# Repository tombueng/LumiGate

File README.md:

# LumiGate

**Art-Net / sACN (E1.31) → DMX512 Gateway** based on ESP32 / ESP32-S3 / WT32-ETH01 with a live web UI, WebSocket push, and manual DMX control via browser.

| Status page | Settings page |
|---|---|
|  |  |

### Web UI walkthrough

A guided tour of every control — manual channel control, labels, sparkline history, identify, blackout, and all settings:

▶ **[Watch the full walkthrough on YouTube](https://youtu.be/up8lIbRqosQ)** &nbsp;·&nbsp; regenerate with [`docs/screenshot.mjs`](docs/screenshot.mjs)

---

## Features

| Feature | Details |
|---|---|
| **Art-Net → DMX512** | Full 512-channel, unicast or broadcast, universe configurable (0–15) |
| **sACN / E1.31 → DMX512** | Multicast receive, universe configurable, runs alongside Art-Net |
| **Protocol selection** | Art-Net only / sACN only / Both — configurable in web UI |
| **Live Web UI** | Bootstrap 5 dark theme, WebSocket push (~10/s), all 512 channels visible |
| **Sender list** | Shows all active Art-Net / sACN senders with per-sender FPS |
| **Conflict detection** | Warning banner when multiple senders are active simultaneously |
| **Jitter stat** | Real-time inter-frame timing deviation (EMA) |
| **Change log** | Live log of DMX value changes with top-N changed channels per frame |
| **Sparkline** | Per-channel history sparkline in the channel detail modal |
| **Channel labels** | Name any channel (e.g. "Front Wash L") — shown in grid, modal, and change log |
| **Identify** | Flash a channel to full for ~1.5 s to physically locate the fixture |
| **Manual DMX control** | Click any channel in browser, set value via slider |
| **Blackout button** | Zero all channels instantly from browser |
| **Art-Net / Manual toggle** | Switch between protocol passthrough and manual override |
| **Failsafe output** | Continuous 40 Hz DMX refresh holds the last frame through brief input gaps |
| **Static IP or DHCP** | Configurable static IP/gateway/subnet/DNS, or automatic DHCP |
| **Mesh-aware WiFi** | Scans all channels and joins the **strongest** AP (multi-AP/mesh friendly) |
| **WiFi Config Portal** | First-boot AP + captive portal via WiFiManager |
| **Versioned OTA** | Pick & install any past release from a table, or auto-update to latest |
| **OTA Updates** | ArduinoOTA (IDE/CLI) + manual `.bin` upload + one-click GitHub update |
| **mDNS** | Reachable as `dmx-gateway.local` (hostname configurable) |
| **REST API** | `GET /dmx.json`, `/senders.json`, `/log.json`, `/version.json`, `/labels.json` |
| **Status LED** | Plain GPIO or WS2812 RGB NeoPixel — color codes WiFi/idle/DMX active state |
| **Up to 2 DMX outputs** | Two independent universes, each its own UART + RS485 transceiver (same universe on both = splitter) |
| **Status display** | Optional I²C OLED (SSD1306 / SH1106) or colour SPI OLED (SSD1351) — IP, universe, FPS, sources + auto-rotating conflict/identify/manual banners |
| **Configurable DMX pins** | Per output: universe, UART port, TX / RX / RTS GPIO — set at runtime via web UI, no recompile |
| **NVS persistence** | Universe, protocol, IP config, labels, hostname, OTA password, LED/DMX pin config survive reboots |
| **Config reset** | Hold BOOT button 3 s on startup, or via `/reset` page |
| **Ethernet support** | WT32-ETH01: wired LAN via LAN8720, no WiFi required, DHCP |
| **Dual/triple target** | Builds for ESP32 (WROOM-32), ESP32-S3 (DevKitC-1), WT32-ETH01 |

---

## Hardware

> ### 🛠 Custom PCB — LumiGate v3
>
> Want the real thing instead of breadboard + modules? There's a complete **open-source 4-layer PCB**:
> ESP32-S3 with **both WiFi and wired Ethernet** (W5500), **galvanically-isolated DMX** output,
> USB-C power + flashing, status LEDs, BOOT/RST buttons, and an optional OLED/TFT display header —
> all palm-sized and fabricable at JLCPCB for a few dollars.
>
> 
>
> **→ Full design, component rationale, BOM, gerbers & JLCPCB fab guide: [`hardware/`](hardware/README.md)**

The rest of this section covers the simpler **breadboard / module** build (an off-the-shelf ESP32 DevKit
+ an isolated RS485 module) — perfect for getting started without fabricating a board.

### Bill of Materials — WiFi build (ESP32 / ESP32-S3)

| # | Component | Description | Link |
|---|---|---|---|
| 1 | **ESP32 DevKit v1** | ESP32-WROOM-32, 30-pin, any CH340/CP2102 variant | [Amazon.de search](https://www.amazon.de/s?k=ESP32+DevKit+WROOM-32) |
| 2 | **Waveshare TTL to RS485 (C)** | Galvanically isolated RS485 transceiver, auto-direction | [Amazon.de – B0D4TZQYVG](https://www.amazon.de/dp/B0D4TZQYVG) |
| 3 | **XLR-5 female panel socket** | Standard DMX output connector (XLR-3 also works) | [Amazon.de search](https://www.amazon.de/s?k=XLR+5+Pin+Buchse+Panel) |
| 4 | **Jumper wires / dupont cables** | Male–male for breadboard, or direct solder | any |
| 5 | **USB-A to Micro-USB cable** | Power + serial flash | any |

### Bill of Materials — Ethernet build (WT32-ETH01)

| # | Component | Description | Link |
|---|---|---|---|
| 1 | **WT32-ETH01** | ESP32 + LAN8720 Ethernet PHY, built-in RJ45 | [Amazon.de search](https://www.amazon.de/s?k=WT32-ETH01) |
| 2 | **Waveshare TTL to RS485 (C)** | Same as WiFi build | [Amazon.de – B0D4TZQYVG](https://www.amazon.de/dp/B0D4TZQYVG) |
| 3 | **XLR-5 female panel socket** | Same as WiFi build | any |
| 4 | **Ethernet cable** | Cat5e or better | any |
| 5 | **5V power supply** (500 mA+) | WT32-ETH01 has no USB port — use a 5V supply on the VIN pin | any |

> The WT32-ETH01 has a built-in RJ45 jack and LAN8720 PHY soldered on-board. No additional Ethernet module needed.

**Optional for enclosure:**
- Project box / DIN-rail enclosure
- 120 Ω termination resistor across DMX A/B at the cable end (required for long runs)

---

### The RS485 Module: Waveshare TTL to RS485 (C)

This module is the key interface between the ESP32's UART and the DMX RS485 bus.

| Property | Value |
|---|---|
| Product name | Waveshare TTL to RS485 (C) |
| Isolation | Galvanic, 2500 V RMS (SP3485 + isolation transformer) |
| Direction control | Automatic — no DE/RE pin needed |
| TTL voltage | 3.3 V or 5 V (VCC selects level) |
| Max baudrate | ≥ 250 kbps (verified working at DMX rate) |
| Connector (TTL side) | 6-pin 2.54 mm header: VCC / GND / RXD / TXD / (unused) / (unused) |
| Connector (RS485 side) | Screw terminal: A / B / GND |
| Dimensions | ~38 × 14 mm |

> **Why galvanic isolation?**  
> DMX fixtures are often powered from separate circuits or have ground loops. The isolated module prevents ground noise from corrupting the signal and protects the ESP32 from voltage spikes.

> **Why auto-direction?**  
> Standard RS485 requires toggling a DE/RE pin to switch between transmit and receive. The Waveshare (C) variant handles this internally based on line activity — no GPIO needed, firmware is simpler. Trade-off: RDM (which requires half-duplex arbitration) is not supported by this module.

---

### Pinout Reference

**Waveshare TTL to RS485 (C) — TTL header (left side):**

```
Pin 1  VCC   → ESP32 3.3V
Pin 2  GND   → ESP32 GND
Pin 3  RXD   → ESP32 GPIO17  (default TX pin — configurable in web /config)
Pin 4  TXD   → ESP32 GPIO16  (default RX pin — configurable in web /config)
Pin 5  —     (not connected)
Pin 6  —     (not connected)
```

> **Different hardware?** If your RS485 module or ESP32 board uses different GPIO pins, change TX/RX under **Settings → DMX Output Pins** in the web UI. No recompile needed.

**Waveshare TTL to RS485 (C) — RS485 screw terminal (right side):**

```
A  →  DMX XLR pin 3  (Data+)
B  →  DMX XLR pin 2  (Data–)
GND→  DMX XLR pin 1  (Shield/Ground)  [optional but recommended]
```

---

### Wiring Diagram

**Connection table:**

| ESP32 pin | → | Module pin | → | XLR pin |
|---|---|---|---|---|
| GPIO17 (TX) | → | RXD | — | — |
| GPIO16 (RX) | ← | TXD | — | — |
| 3.3V | → | VCC | — | — |
| GND | → | GND | — | — |
| — | — | A (RS485+) | → | Pin 3 |
| — | — | B (RS485–) | → | Pin 2 |
| GND | — | GND | → | Pin 1 (optional) |

#### WT32-ETH01 wiring (different pins — GPIO16 used by LAN8720)

| WT32-ETH01 pin | → | Module pin | → | XLR pin |
|---|---|---|---|---|
| GPIO4 (TX) | → | RXD | — | — |
| GPIO5 (RX) | ← | TXD | — | — |
| 3.3V | → | VCC | — | — |
| GND | → | GND | — | — |
| — | — | A (RS485+) | → | Pin 3 |
| — | — | B (RS485–) | → | Pin 2 |

> **Do not use GPIO16 or GPIO17 on the WT32-ETH01** — they are connected to the LAN8720 Ethernet PHY (power and RMII).

---

### Assembly Guide

#### Step 1 — Prepare the ESP32

No soldering required if using a DevKit with pre-soldered headers. Place it on a breadboard or in your enclosure.

#### Step 2 — Connect ESP32 ↔ RS485 module

Using dupont jumper wires:

| Color convention | From | To |
|---|---|---|
| Red | ESP32 **3.3V** | Module **VCC** |
| Black | ESP32 **GND** | Module **GND** |
| Yellow | ESP32 **GPIO17** (TX) | Module **RXD** |
| Green | ESP32 **GPIO16** (RX) | Module **TXD** |

> Use **3.3V**, not 5V — the ESP32's GPIOs are not 5V tolerant.

#### Step 3 — Wire the XLR connector

The DMX standard uses XLR-5 (5-pin), but most DMX fixtures also accept XLR-3. Pin numbering is the same:

| XLR Pin | Signal | RS485 module |
|---|---|---|
| 1 | Shield / GND | Module GND (optional) |
| 2 | DMX Data– | Module **B** |
| 3 | DMX Data+ | Module **A** |
| 4 | (unused in DMX) | — |
| 5 | (unused in DMX) | — |

Screw the wires into the RS485 module's terminal block firmly.

#### Step 4 — Termination resistor (for longer cable runs)

For DMX cable runs over ~10 m, solder a **120 Ω resistor** between pins 2 and 3 (A and B) at the **far end** of the DMX chain (i.e., inside the last fixture's XLR input). Most professional fixtures include this internally.

#### Step 5 — Power

The ESP32 DevKit is powered via its **Micro-USB port**. Any 5V USB power supply works (500 mA is sufficient). The RS485 module draws its power from the ESP32's 3.3V rail.

---

### Notes

- **Do not connect DE/RE** — the Waveshare (C) handles direction automatically. Connecting them will break transmission.
- **Keep TTL wires short** (< 20 cm). Long unshielded wires on the TTL side pick up noise; the RS485 side handles long distances natively.
- **XLR gender:** Use a **female** XLR panel socket for the DMX output. DMX sources (transmitters) use female XLR; receivers use male XLR. LumiGate is a source.

---

## Software Stack

| Library | Purpose |
|---|---|
| `someweisguy/esp_dmx ^4.1` | DMX512 transmit via UART |
| `rstephan/ArtnetWifi ^1.5` | Art-Net UDP receiver (port 6454) |
| `tzapu/WiFiManager ^2.0` | WiFi config portal |
| `ESP32Async/ESPAsyncWebServer` | Non-blocking HTTP server + WebSocket (port 80) |
| `ESP32Async/AsyncTCP` | Async TCP backend (runs networking off the main loop) |
| `adafruit/Adafruit NeoPixel ^1.12` | WS2812 RGB status LED support |
| `ArduinoOTA` | OTA firmware updates |
| `ESPmDNS` | mDNS (`dmx-gateway.local`) |
| `Preferences` | NVS persistent config |
| *(built-in UDP)* | sACN / E1.31 multicast receive (port 5568) |

---

## Flashing Pre-built Firmware

No toolchain needed. GitHub CI builds the firmware on every push to master.

**[Download latest release](https://github.com/tombueng/LumiGate/releases/tag/latest)** — includes `firmware.bin`, `bootloader.bin`, `partitions.bin`, `boot_app0.bin`.

### Boot mode (required for all methods)

You must manually enter download mode before flashing:

1. Hold **BOOT** button
2. Press and release **EN** (or **RST**) while keeping BOOT held
3. Release BOOT — the chip is now in download mode
4. Run the flash command

> **ESP32-S3 DevKitC-1:** use the **USB-UART** port (labeled on the board), not the native USB port. The native USB port cannot be used with esptool.

### Windows — one-liner (PowerShell)

Downloads and runs [`flash.ps1`](flash.ps1), which installs Python + esptool automatically:

```powershell
Set-ExecutionPolicy -Scope Process Bypass; irm https://raw.githubusercontent.com/tombueng/LumiGate/master/flash.ps1 | iex
```

Or save and run it manually:

```powershell
# Download
Invoke-WebRequest https://raw.githubusercontent.com/tombueng/LumiGate/master/flash.ps1 -OutFile flash.ps1
# Run
Set-ExecutionPolicy -Scope Process Bypass
.\flash.ps1
```

The script: installs Python 3 via `winget` if missing → installs `esptool` via pip → downloads the four firmware blobs from the latest GitHub release → lets you pick a COM port → guides you through boot mode → flashes.

### macOS / Linux — ESP32 (WROOM-32)

```bash
pip install esptool

REPO=tombueng/LumiGate
for f in firmware.bin bootloader.bin partitions.bin boot_app0.bin; do
  curl -sL "$(curl -s https://api.github.com/repos/$REPO/releases/tags/latest \
    | python3 -c "import sys,json; assets=json.load(sys.stdin)['assets']; \
      print(next(a['browser_download_url'] for a in assets if a['name']=='$f'))")" -o $f
done

# Enter boot mode first (see above), then:
esptool.py --chip esp32 --port /dev/ttyUSB0 --baud 460800 \
  --before default_reset --after hard_reset \
  write_flash -z --flash_mode dio --flash_freq 80m \
  0x1000 bootloader.bin 0x8000 partitions.bin \
  0xe000 boot_app0.bin 0x10000 firmware.bin
```

### macOS / Linux — ESP32-S3 (DevKitC-1)

> **Important:** bootloader goes at `0x0000` on S3 (not `0x1000` like the original ESP32).

```bash
pip install esptool

REPO=tombueng/LumiGate
for f in firmware-esp32s3.bin bootloader-esp32s3.bin partitions-esp32s3.bin boot_app0.bin; do
  curl -sL "$(curl -s https://api.github.com/repos/$REPO/releases/tags/latest \
    | python3 -c "import sys,json; assets=json.load(sys.stdin)['assets']; \
      print(next(a['browser_download_url'] for a in assets if a['name']=='$f'))")" -o $f
done

# Enter boot mode first, use the USB-UART port, then:
esptool.py --chip esp32s3 --port /dev/ttyUSB0 --baud 921600 \
  --before default_reset --after hard_reset \
  write_flash -z --flash_mode dio --flash_freq 80m \
  0x0000 bootloader-esp32s3.bin 0x8000 partitions-esp32s3.bin \
  0xe000 boot_app0.bin 0x10000 firmware-esp32s3.bin
```

> Replace `/dev/ttyUSB0` with your port (`/dev/tty.usbserial-*` on macOS).

### macOS / Linux — WT32-ETH01

```bash
pip install esptool

REPO=tombueng/LumiGate
for f in firmware-wt32eth01.bin bootloader-wt32eth01.bin partitions-wt32eth01.bin boot_app0.bin; do
  curl -sL "$(curl -s https://api.github.com/repos/$REPO/releases/tags/latest \
    | python3 -c "import sys,json; assets=json.load(sys.stdin)['assets']; \
      print(next(a['browser_download_url'] for a in assets if a['name']=='$f'))")" -o $f
done

# Enter boot mode (hold BOOT + press RST), then:
esptool.py --chip esp32 --port /dev/ttyUSB0 --baud 460800 \
  --before default_reset --after hard_reset \
  write_flash -z --flash_mode dio --flash_freq 80m \
  0x1000 bootloader-wt32eth01.bin 0x8000 partitions-wt32eth01.bin \
  0xe000 boot_app0.bin 0x10000 firmware-wt32eth01.bin
```

---

## Build & Flash

### Requirements

- [PlatformIO](https://platformio.org/) with VS Code extension
- ESP32 connected via USB (CH340 or CP2102)

### Project Structure

```
LumiGate/
├── src/
│   ├── main.cpp          ← firmware logic
│   ├── pages/            ← edit web UI here (plain HTML)
│   │   ├── index.html
│   │   ├── config.html
│   │   ├── config_saved.html
│   │   ├── reset.html
│   │   └── reset_done.html
│   ├── assets/           ← images served by the ESP32
│   │   └── logo.png      ← 96×96 px, replaces itself on rebuild
│   └── generated/        ← auto-created at build time, gitignored
├── docs/                 ← documentation assets (README images)
├── extra_scripts.py      ← PlatformIO pre-build hook
└── platformio.ini
```

### How the build pipeline works

Before every `pio run`, PlatformIO executes `extra_scripts.py`, which:

1. Reads every `src/pages/*.html` file
2. Reads every `src/assets/*.png` file
3. Converts them to C `PROGMEM` arrays / string literals and writes them to `src/generated/*.h`
4. `main.cpp` `#include`s those headers — the HTML and images become part of the firmware binary

**To change the web UI**, edit the HTML files in `src/pages/` and rebuild — no C++ changes needed.  
**To replace the logo**, drop a new 96×96 PNG into `src/assets/logo.png` and rebuild.

Dynamic values (IP address, universe number, etc.) use `{{PLACEHOLDER}}` tokens in the HTML; `main.cpp` substitutes them at request time with `String::replace()`.

### First Flash (USB)

```bash
pio run --target upload
```

> **If upload fails** ("Wrong boot mode"): Hold **BOOT** button, tap **EN/RST**, release BOOT — chip enters download mode. Then retry upload.

### OTA Updates (after first flash)

- **From browser:** open `http://dmx-gateway.local/config` → Firmware Update section → upload a `.bin` file or click "Update from GitHub"

| Downloading update | Back online |
|---|---|
|  |  |

- **From IDE:** uncomment in `platformio.ini`:
```ini
upload_protocol = espota
upload_port     = dmx-gateway.local
upload_flags    = --auth=dmxota
```

---

## First Setup

### WT32-ETH01 (Ethernet)

No configuration needed. Connect an Ethernet cable, power on — DHCP assigns an IP automatically. Open `http://dmx-gateway.local` or check your router for the assigned IP. There is no WiFi portal.

### 1. Config Portal (WiFi builds only)

On first boot (or after WiFi reset), LumiGate opens a WiFi access point:

- **SSID:** `DMX-Gateway` (no password)
- Connect with phone or PC → browser auto-opens portal (or go to `192.168.4.1`)
- Select your network, enter password, set Art-Net Universe (default: `0`)
- Click **Save** → LumiGate connects and reboots

> **Mesh / multi-AP WiFi:** LumiGate scans all channels and joins the
> **strongest** AP for your SSID (and re-picks it on reconnect), so it won't
> latch onto a distant node. The ESP32 is **2.4 GHz only** — make sure the AP
> nearest the device broadcasts 2.4 GHz. Check `rssi` on the status page: a
> healthy link is roughly −40 to −65 dBm. If it sits near −80 dBm right next to
> a router, the nearby node likely isn't offering 2.4 GHz — use a dedicated
> 2.4 GHz IoT SSID, or the **WT32-ETH01 (Ethernet) build** for a wired,
> rock-solid connection.

### 2. Status Page

Open `http://dmx-gateway.local` (or the IP shown in serial monitor at 115200 baud):

- Live stats: framerate, RSSI, uptime, free heap, jitter
- Conflict warning if multiple senders are detected
- Active sender list with per-sender protocol and FPS
- All 512 DMX channels as a color-coded grid (cyan = active)
- Click any cell → slider + sparkline history appear → set value directly
- Change log with recent DMX activity

### 3. Changing WiFi / Config Reset

To move LumiGate to a different WiFi network, clear its stored credentials — it will reopen the setup portal on next boot.

| Method | Steps |
|---|---|
| **Web** (easiest) | Open `http://dmx-gateway.local/reset` → click **Reset WiFi** → device reboots into AP mode |
| **Hardware** | Power off → hold **BOOT** → power on → keep holding for 3 seconds → release → device reboots into AP mode |

After reset, connect to the `DMX-Gateway` access point (no password) and follow the [First Setup](#1-config-portal) steps to join the new network.

---

## Web UI

The HTTP server and WebSocket are served by ESPAsyncWebServer (non-blocking),
so the web UI never stalls DMX output. Pages are gzip-compressed and dynamic
values are fetched as JSON.

| URL | Method | Function |
|---|---|---|
| `/` | GET | Live status + 512-channel DMX grid (gzip) |
| `/config` | GET / POST | Change universe, protocol, static IP, hostname, OTA password, LED config, DMX pins (gzip) |
| `/reset` | GET / POST | Clear WiFi credentials, reboot to AP mode |
| `/info.json` | GET | Current settings + status (SSID, IP, universe, version, etc.) |
| `/dmx.json` | GET | All 512 values, fps, rssi, uptime, heap, manual mode flag |
| `/senders.json` | GET | Active Art-Net / sACN senders (also pushed over the WebSocket) |
| `/log.json` | GET | Recent DMX change log entries (also pushed over the WebSocket) |
| `/labels.json` | GET | Channel labels object |
| `/labels` | POST | Store the full labels object (JSON body) |
| `/version.json` | GET | Current firmware version + update-available flag |
| `/autoupdate` | POST | Toggle auto-update (`enabled=0/1`) |
| `/ota/upload` | POST | Upload and flash a local `firmware.bin` |
| `/ota/github` | POST | Install a release from GitHub (`version=latest` or `1.0.N`) |

### WebSocket (`ws://<device>/ws`, port 80)

Binary status/DMX frame pushed ~10×/s (528 bytes):

```
Bytes  0–1    fps × 10           uint16 big-endian
Bytes  2–3    RSSI (dBm)         int16  big-endian
Bytes  4–7    free heap          uint32 big-endian
Bytes  8–11   uptime (s)         uint32 big-endian
Byte   12     active sender count uint8
Byte   13     conflict flag       uint8 (1 = multiple senders)
Bytes  14–15  jitter × 10 (ms)   uint16 big-endian
Bytes  16–527 DMX ch 1–512       uint8[512]
```

A JSON **text** frame with the sender list + change log is pushed every 2 s
(`{"meta":1,"senders":[…],"log":[…]}`) so the browser never has to poll.

Browser → ESP32 (JSON text):
```json
{ "type": "set",      "ch": 1,  "val": 200 }
{ "type": "mode",     "manual": true       }
{ "type": "blackout"                       }
{ "type": "identify", "ch": 5              }
```

Channel labels are managed over REST (`GET /labels.json`, `POST /labels`).

---

## QLC+ Setup

1. Open **Eingänge/Ausgänge** tab
2. Click in the output area right of **Universe 1** → select **ArtNet** → interface = your PC's IP
3. Configure: Output IP = LumiGate's IP, Art-Net Universe = `0`
4. Set transmission mode to **Full** (sends all 512 channels continuously at ~40 fps)
5. Test with **Einfaches Mischpult** → move fader → grid lights up cyan

> **Universe mapping:** QLC+ "Universe 1" = Art-Net Universe `0`. LumiGate defaults to Universe `0`.  
> **Tip:** if "Standard" mode shows ~0.4 fps and values don't update, restart QLC+ or switch to "Full" mode.

### Ready-made demo shows

Two QLC+ workspaces are included to test fixtures and show off the gateway — open with **File → Open**, map Universe 1 → ArtNet (above), switch to **Operate** mode, and press the Virtual Console buttons:

| File | Description |
|---|---|
| [`docs/qlcplus-demo.qxw`](docs/qlcplus-demo.qxw) | Small 6-channel demo: fade, blink, running light |
| [`docs/qlcplus-show.qxw`](docs/qlcplus-show.qxw) | **30-minute, 20-channel show** — sine waves, comets, sparkle, VU bounce, crossfades, strobes, build-ups and more, sequenced into an intro→build→peak→groove→outro arc. Press **GREAT SHOW**. |

The big show is generated by [`docs/make_show.py`](docs/make_show.py) — edit the `arc` list and re-run to customize.

---

## Status LED

LumiGate supports two LED types, configurable in the web UI:

| State | WS2812 RGB | Plain GPIO |
|---|---|---|
| Booting | white | on |
| Connecting to WiFi | blue blink | blink |
| Config portal / AP active | purple | on |
| No WiFi (lost) | red blink (fast) | off |
| Idle (connected, no DMX) | amber heartbeat (½ s on/off) | pulse |
| DMX active | solid green | solid |

The "DMX active" green is held through brief input gaps (continuous 40 Hz
output), so momentary multicast loss doesn't flicker the LED. The LED runs on
its own task, so serving the web UI never freezes it.

Default GPIO: `2` (ESP32 DevKit on-board LED). ESP32-S3 DevKitC-1 uses GPIO `48` (built-in WS2812).

---

## Display (OLED / colour OLED)

LumiGate can drive an **optional status display** that shows the gateway's live state
without a browser — IP, universe, protocol, frame rate, source count and link / DMX
activity — and **auto-switches to a full-screen alert** when something needs attention
(two consoles fighting over the universe, identify, or manual override). It's **off by
default**; enable and pin it under **Settings → Display**.

*Rendered from the firmware's own layout code with the real display font. **Top:** 0.96″ /
1.3″ mono OLED (status, then the conflict / identify / manual banners). **Middle:** the same
panel in blue and yellow/blue-split, and the 0.91″ 128×32 compact layout. **Bottom:** the
1.5″ SSD1351 colour panel, which mirrors the RGB status-LED language (green = live,
amber = idle, red = conflict).*

### Supported panels

| Panel | Controller | Bus | Pins | Boards |
|---|---|---|---|---|
| 0.96″ / 1.3″ OLED 128×64 | SSD1306 / SH1106 | I²C | 2 | all |
| 0.91″ OLED 128×32 | SSD1306 | I²C | 2 | all |
| 1.5″ colour OLED 128×128 | SSD1351 | SPI | ~5 | ESP32 / ESP32-S3 (not the Ethernet boards) |

Mono panels are 1-bit — white, blue and yellow/blue-split versions all behave identically
(the colour is the physical emitter, not addressable). The I²C address is auto-detected
(`0x3C` / `0x3D`). SPI colour panels need ~5 pins, so they only fit the non-Ethernet boards.

### Settings (Settings → Display)

| Field | Notes |
|---|---|
| Display type | off / SSD1306 128×64 / SSD1306 128×32 / SH1106 128×64 / SSD1351 colour |
| SDA, SCL | I²C pins (mono panels). Avoid strapping pins like GPIO12; WT32-ETH01 → `14` / `15` |
| CS, DC, RST, SCK, MOSI | hardware-SPI pins (colour panel) |
| Orientation | normal / flipped 180° |

See [docs/display.md](docs/display.md) for the full design — per-board pin tables and layout details.

---

## DMX Outputs

LumiGate drives up to **2 independent DMX outputs** — each its own universe, UART port and
RS485 transceiver — configurable at runtime under **Settings → DMX Outputs** (no recompile).
The 2-output ceiling is a hardware limit: the ESP32 / ESP32-S3 expose 3 UARTs and UART0 is the
serial console, leaving UART1 + UART2. **Output B ships disabled**, so single-universe setups are
unchanged, and devices updated from older firmware keep their existing output as Output A.

Per output:

| Setting | Default (Output A / B) | Description |
|---|---|---|
| Enabled | A on / B off | Whether this output drives a DMX line |
| Universe | `0` / `1` | Art-Net universe (sACN universe = this + 1). Range 0–15 |
| UART port | `1` / `2` | Which ESP32 UART drives the line. Each enabled output needs a **distinct** port |
| TX pin | `17` (GPIO17) | ESP32 GPIO that drives the RS485 module's DI (data-in) |
| RX pin | `16` (GPIO16) | ESP32 GPIO connected to the RS485 module's RO (data-out); needed for RDM |
| RTS / DE pin | `−1` (disabled) | RS485 direction-control pin. −1 for auto-direction modules (Waveshare C). Required for RDM. |

Setting **both outputs to the same universe** turns LumiGate into a 1-in / 2-out DMX splitter.
**RDM** runs on the first enabled output with an RTS pin set (one output at a time). For
multi-universe input, **Art-Net is recommended** (single UDP socket, no IGMP); sACN works too
(one multicast group joined per universe).

> **WT32-ETH01:** the Ethernet PHY consumes most GPIOs, so a second output is best run
> output-only (TX, no RX/RDM).

### Per-board defaults & capabilities

Applied on first boot; everything is overrideable in the web UI (no recompile).

| Board | Build env | Net | Outputs | Output A — TX / RX / RTS | Suggested Output B | Notes |
|---|---|---|---|---|---|---|
| ESP32 DevKit (WROOM-32) | `esp32dev` | WiFi | 2 | GPIO17 / 16 / −1 | UART2, TX 32, RX 33 | Plenty of free GPIO; RDM possible on both |
| ESP32-S3 DevKitC-1 | `esp32s3dev` | WiFi | 2 | GPIO17 / 16 / −1 | UART2, TX 18 (RX −1) | LED = WS2812 on GPIO48 |
| WT32-ETH01 | `wt32eth01` | Ethernet | 2 | GPIO4 / 5 / −1 | UART2, TX-only | GPIO16 = LAN8720 PHY power, so pins are shifted; 2nd output best TX-only (no RX/RDM) |

> **All three boards drive two outputs** (UART1 + UART2). A 2nd output (UART2) used to panic on the
> ESP32-S3 — a latent **esp_dmx 4.1.0 bug** where the UART2 entry was guarded by an enum the
> preprocessor reads as 0, so it was compiled out (null peripheral pointer). Fixed by a build-time
> patch in [`extra_scripts.py`](extra_scripts.py).

**ESP32-S3 — safe GPIOs for a 2nd output:** free choices are **5, 6, 7, 8, 15, 18, 21**. Avoid
**26–37** (SPI flash / octal PSRAM — *will* crash), **19/20** (USB), **43/44** (serial console),
**0/45/46** (strapping), **48** (WS2812 LED), and Output A's **16/17**.

**Using a different RS485 module?** Wire your module's DI (data-in) to the TX GPIO and RO (data-out)
to the RX GPIO, then set the pins under Settings → DMX Outputs.

### Upgrade & crash safety

- **Existing single-universe devices are unaffected by the update.** Migration maps the old
  single-output config to **Output A** and leaves **Output B disabled**, so exactly one driver is
  installed on UART1 — byte-for-byte the same path as before.
- **No configuration can brick the device.** A safe-boot guard persists a crash counter around DMX
  init; if init ever panics (a bad pin/port), the next boots progressively disable outputs (keep
  A → all off) until the web UI is reachable. An enabled output with no TX pin is sanitized off
  automatically (firmware + a client-side check).

---

## Persistent Configuration (NVS)

| Key | Default | Change via |
|---|---|---|
| Art-Net Universe | `0` | Web `/config` or portal |
| Protocol | `Both (Art-Net + sACN)` | Web `/config` |
| Static IP / gateway / subnet / DNS | DHCP | Web `/config` (Network) |
| Auto-update | off | Web `/config` (Firmware) |
| Channel labels | — | Status page (channel modal) |
| Hostname | `dmx-gateway` | Web `/config` |
| OTA Password | `dmxota` | Web `/config` |
| LED type / GPIO pin | board default | Web `/config` (Status LED) |
| Per-output: enabled / universe / UART port / TX / RX / RTS | A on (uni 0, UART1, TX=17, RX=16, RTS=−1); B off | Web `/config` (DMX Outputs) |
| Display type / pins | off | Web `/config` (Display) |
| WiFi credentials | — | Config portal or `/reset` |

---

## Testing

End-to-end Playwright tests drive a **live device** — they inject real Art-Net and sACN/E1.31
packets over the network and assert the REST API, WebSocket and web UI react correctly (Art-Net/sACN
→ DMX, sender tracking, conflict banner, change log, manual override + blackout, labels, and the
2-output feature). See [`docs/tests/README.md`](docs/tests/README.md).

```bash
cd docs && npm install && npx playwright install chromium
LUMIGATE_HOST=dmx-gateway.local npm test
```

---

## License

MIT — do whatever you want, attribution appreciated.

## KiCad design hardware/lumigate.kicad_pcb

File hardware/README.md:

# LumiGate v3 — hardware

A compact, open-source **Art-Net / sACN → galvanically-isolated DMX512 gateway**, built around
an ESP32-S3 with **both** WiFi *and* wired Ethernet. Designed entirely as code (SKiDL netlist) and
routed by a fully-scripted, placement-driven pipeline — so the board regenerates itself from your
component placement, isolation barrier and all.

---

## What problem does it solve?

Lighting consoles and media servers speak **Art-Net** or **sACN (E1.31)** over a network. Fixtures —
dimmers, moving heads, hazers, LED bars — speak **DMX512** over an isolated RS-485 bus. LumiGate sits
between them: it receives Art-Net/sACN over WiFi or Ethernet and emits a clean, **opto-isolated DMX512**
signal. It's the box that lets you drive a rack of conventional stage gear from QLab, a grandMA, or any
Art-Net source — without dragging a laptop and a USB-DMX dongle around backstage.

The whole device runs on a single ESP32-S3, fits on a board you can hold in your palm, and costs a few
dollars to fabricate at JLCPCB.

---

## Headline design decisions (the "why")

| Decision | Why |
|---|---|
| **ESP32-S3** as the MCU | Plenty of GPIO, fast dual-core, native USB, mature Arduino/IDF support, and cheap. The N8 variant (no PSRAM) **frees up GPIO33–37**, which we need for the LEDs + display. |
| **W5500 SPI Ethernet** (not the ESP's RMII) | The S3 has **no built-in Ethernet MAC** (unlike the original ESP32), so RMII/LAN8720 is physically impossible. The W5500 is a self-contained TCP/IP-offload Ethernet controller on SPI — the *only* practical wired-Ethernet path for the S3. Wired Ethernet matters: a packed venue's 2.4 GHz band is hostile, and a show can't drop frames. |
| **Galvanically-isolated DMX** | DMX runs long cables between gear sitting on different mains circuits with different ground potentials. Without isolation you get **ground loops** (noise, flicker) and, worse, **fault currents** that can destroy the gateway when something downstream shorts. Pro DMX gear is *always* isolated. We isolate both the data (ISO3086) and the power feeding it (B0505S DC-DC), so the DMX domain shares **no copper** with the logic side. |
| **USB-C** | Reversible, modern, and carries both **power and native flashing** — one cable to power and program. |
| **4-layer PCB** | A solid inner ground plane gives the W5500's Ethernet pairs a 100 Ω reference, tames EMI, and makes the dense routing actually fit. (More below.) |

---

## The components, in detail

### Brains & networking
- **U1 — ESP32-S3-WROOM-1-N8** *(LCSC C2913198)* — the MCU + 2.4 GHz WiFi radio. Runs the Art-Net/sACN
  receiver, the web UI, OTA updates, and the DMX engine. The PCB antenna hangs over the left board edge
  (no copper underneath it — intentional, for radiation efficiency).
- **U2 — WIZnet W5500** *(C32843)* + **Y1 — 25 MHz crystal** + **J3 — HR961160C RJ45 MagJack** *(C55683)* —
  a complete 10/100 wired-Ethernet subsystem on SPI. The magjack integrates the isolation magnetics and
  the link/activity LEDs. (Ethernet is isolated by the magjack's transformers; the W5500's current-mode
  TX center-tap is correctly biased to 3V3.)

### Isolated DMX output
- **U5 — TI ISO3086DWR** *(C183095)* — an **isolated RS-485 transceiver**. The DMX driver and the logic
  that controls it are separated by a silicon isolation barrier rated for kilovolts. Wired 2-wire
  (Y↔A, Z↔B bridged) for standard DMX512.
- **PS1 — B0505S-1W** *(C7465127)* — an **isolated 5 V→5 V DC-DC** module that powers the *secondary*
  side of U5. Because both the data path **and** its power are isolated, the DMX connector shares no
  ground with the rest of the board.
- **D1 — SM712 TVS** *(C404012)* + **R12 — 120 Ω termination** — surge protection clamped to the DMX-side
  ground, and the standard RS-485 line termination.
- **J1 — XLR-3** *(C309326)* — the DMX output connector, living entirely on the isolated domain.

### Power
- **U4 — SY8089 buck** *(C78988)* + **L1 — 2.2 µH** — steps the USB-C 5 V down to **3.3 V**. The feedback
  divider is **R10 = 45.3 kΩ / R11 = 10 kΩ → 3.318 V** (SPICE-verified). Powers everything on the logic side.

### Programming & USB
- **U3 — CH340C** *(C84681)* + **J2 — USB-C** *(C165948)* — USB-to-UART for flashing, plus the power inlet.
- **Q1/Q2 — MMBT3904** *(C20526)* — the classic **2-transistor auto-reset** circuit: the CH340's DTR/RTS
  toggle EN and IO0 so `esptool` can drop the chip into the bootloader automatically — no button-dance.

### User interface & features
- **D2–D6 — 5 status LEDs** (red/green/yellow/blue/white) wired straight to GPIOs (IO1/2/6/7/15): network
  state, DMX activity, source-conflict, identify — at-a-glance status without a screen.
- **SW1 (BOOT) / SW2 (RST)** — `B3U-1000P` tact switches *(C231329)*. BOOT doubles as the config-portal /
  factory-reset button in firmware; RST is a hard reset.
- **J4 — JST SH 1.0 mm 9-pin display header** — an **optional on-board OLED/TFT status panel** connector.
  Carries **both** I²C (SDA/SCL → for SSD1306/SH1106 mono OLEDs) **and** SPI (SCK/MOSI/CS/DC/RST → for
  SSD1351 colour OLED / ST7789 TFT) on free, non-strapping GPIOs. JST SH is tiny and uses widely-available
  pre-crimped cables. *(Optional — populate only if you want the panel.)*

---

## Feature summary

- 🎛 **Art-Net + sACN (E1.31)** input, configurable universe
- 🌐 **Dual connectivity** — WiFi (captive-portal setup) *and* wired Ethernet (W5500)
- ⚡ **Galvanically-isolated DMX512 output** (RDM-capable transceiver)
- 🖥 **Optional OLED/TFT status display** (I²C or SPI, via the JST header)
- 💡 **5 status LEDs** + BOOT/RST buttons
- 🔌 **USB-C** — single-cable power + native flashing, plus **OTA** updates
- 🟢 Open hardware, ~palm-sized, JLCPCB-assemblable for a few dollars

---

## The 4-layer board & the isolation barrier

**Stack-up:** 4-layer, JLCPCB's standard **JLC04161H-3313** (1.6 mm). The two inner layers are
**ground-filled signal layers** — not classic "power planes". That's deliberate: as signal layers the
autorouter will happily route ground (and fine-pitch escapes) to the inner copper, while the fill still
gives every trace a solid 0.21 mm-away reference. The result: clean ~100 Ω Ethernet pairs and good EMI.

**Isolation:** the DMX domain (`GNDISO`, `VISO`, `DMX_A`, `DMX_B`) is held **≥ 4 mm** from all other
copper by a net-based rule in [`lumigate.kicad_dru`](lumigate.kicad_dru). The two isolation parts whose
own pins are inherently close — **PS1** (B0505S, 2.5 mm pin pitch) and **U5** (ISO3086) — are
*courtyard-exempted* (their isolation is internal/rated), exactly as the USB-C connector's fine-pitch
pads are. The inner ground planes are **notched** away from the isolated region so no inner copper ever
crosses the barrier.

---

## Design-as-code & the routing pipeline

The board is **generated, not hand-drawn**. [`lumigate.py`](lumigate.py) is a [SKiDL](https://github.com/devbisme/skidl)
netlist — the single source of truth for every part and connection. From a placement, the rest is scripted
and **adapts to wherever you put the parts**:

```text
1. place / move parts in KiCad   →  save
2. python rebuild_iso.py         # regenerates inner GND planes + GNDISO pour + iso keepout
                                 #   from the LIVE part positions — no hardcoded coordinates
3. python escape_connectors.py   # escapes the few fine-pitch connector pins to LOCKED vias
4. python autoroute_fr2.py       # Freerouting 2.2.4 routes the whole board, keeping locked escapes
5. python cleanup_pads.py        # mounting posts → NPTH, widen tight THT annular rings
```

Run everything with the **KiCad 10 bundled Python** (it ships `pcbnew`). `autoroute_fr2.py` drives
**Freerouting 2.2.4**, which needs **Java 25+**; the jar and a portable JDK live in `tools/` (git-ignored).
Locked tracks survive every re-route (KiCad exports them as DSN `(type fix)`), so connector escapes only
get done once. Move a part, re-run — done.

---

## Fabricating it at JLCPCB

Everything you upload is already generated in this folder.

### 1 — Bare PCB
1. Go to [jlcpcb.com](https://jlcpcb.com) → **Add gerber file** → upload **`lumigate_gerbers.zip`**.
2. It auto-detects **4 layers**. Set: **Layers = 4**, Thickness **1.6 mm**, Impedance control =
   **JLC04161H-3313** stackup (the one this board is designed for). Surface finish your choice (ENIG
   recommended for the fine-pitch parts).

### 2 — Assembly (SMT)
3. Enable **PCB Assembly**, then upload:
   - **BOM** → `lumigate_BOM_jlcpcb.csv`
   - **CPL / pick-and-place** → `lumigate_CPL.csv`
4. In the BOM matching step, confirm each LCSC part (they're pre-filled). **J4** (the optional display
   header) has no LCSC assigned — either pick a JST SH 9-pin part there or mark it **Do Not Populate**.
5. **Review the placement preview** — the CPL is rotation/position-corrected by `gen_cpl.py`, so parts
   should sit correctly. The ESP32-S3's antenna intentionally overhangs the left edge.

### 3 — Through-hole parts
The XLR (J1), USB-C (J2), MagJack (J3) and B0505S (PS1) are through-hole. Either add JLCPCB's through-hole
assembly or hand-solder them — they're all large, easy joints.

### Cost ballpark
4-layer, this size, 5 pcs ≈ **a few dollars** for the bare boards; SMT assembly adds the parts + a setup
fee. A complete, assembled prototype lands well under typical hobby budgets.

---

## Files

| File | What |
|---|---|
| `lumigate.py` | **SKiDL source** — authoritative netlist (`python lumigate.py` → `lumigate.net`) |
| `lumigate.kicad_pcb` / `.kicad_pro` | the board + KiCad project |
| `lumigate.kicad_dru` | custom design rules — the 4 mm DMX isolation + connector exemptions |
| `rebuild_iso.py` · `escape_connectors.py` · `autoroute_fr2.py` · `cleanup_pads.py` | the routing pipeline |
| `route.py` · `autoroute.py` | older Freerouting-1.9 fallbacks (no Java 25 needed) |
| `gen_bom_from_board.py` → `lumigate_BOM_jlcpcb.csv` | JLCPCB assembly BOM |
| `gen_cpl.py` → `lumigate_CPL.csv` / `.xlsx` | JLCPCB pick-and-place (corrected) |
| `lumigate_gerbers.zip` | 4-layer gerbers + PTH/NPTH drill — the fab upload |
| `easyeda/` | LCSC/easyeda footprints + 3D models for the specific parts |
| `tools/` | Freerouting 2.2.4 jar + portable JDK 25 *(git-ignored — see Toolchain)* |
| `board-pcb-1.png` · `board3d-1.png` · `board3d-2.png` | layout + 3D renders |

## Status

**Electrically production-ready & validated:** 0 unconnected, 0 shorts, **0 isolation (4 mm) violations**,
SPICE-validated analog (buck 3.318 V, EN reset-RC 13.9 ms, auto-reset sequence, LED currents). A handful
of minor connector/edge DRC warnings remain (J3 magjack mask slivers, USB-C unused-pad clearance) — these
are inherent to the manufacturer footprints and are cleared in a short GUI pass or simply waived at the
JLCPCB upload step.

## Toolchain

- **KiCad 10** (bundled `python` + `kicad-cli`)
- **Java 25+** — [Temurin JDK 25](https://adoptium.net/temurin/releases/?version=25) (portable zip → `tools/`)
- **Freerouting 2.2.4** — [release jar](https://github.com/freerouting/freerouting/releases/tag/v2.2.4) → `tools/`
- **SKiDL** (`pip install skidl`) to regenerate the netlist

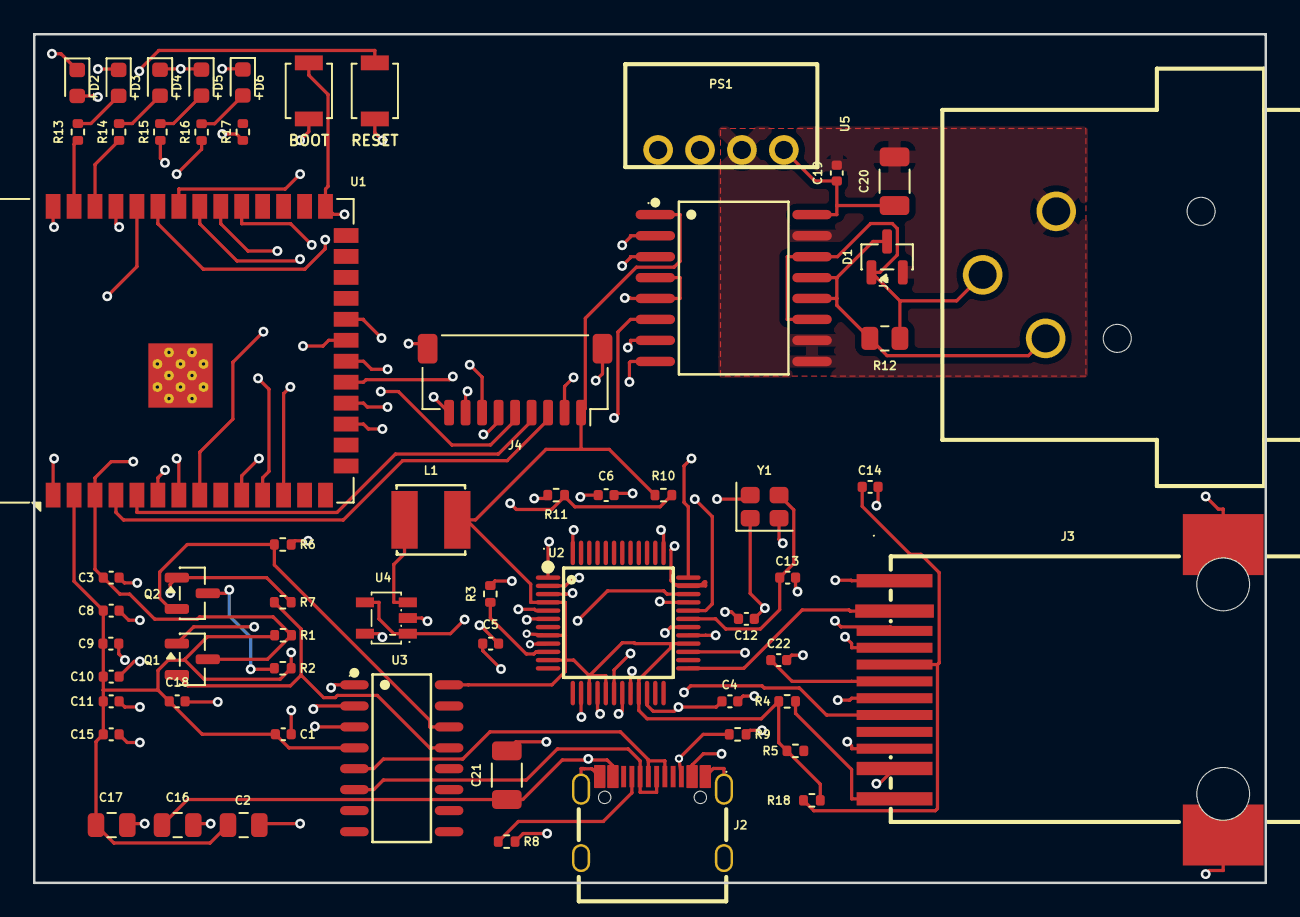
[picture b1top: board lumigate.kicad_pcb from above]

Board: 4 copper layers, 74.6 x 51.4 mm, 61 parts (0 on the bottom side), 61 nets.

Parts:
C1, C5, C8, C9, C10, C11, C14, C15, C18, C19, C22: 100nF; C_0402_1005Metric
C2: 10uF; C_0805_2012Metric
C3, C4: 1uF; C_0402_1005Metric
C6: 4.7uF; C_0402_1005Metric
C12, C13: 22pF; C_0402_1005Metric
C16, C17: 22uF; C_0805_2012Metric
C20, C21: 10uF; C_1206_3216Metric
D1: SM712; SOT-23
D2, D3, D4, D5, D6: LED; LED_0603_1608Metric
J1: XLR-3 out; CONN-TH_XLR-328P
J2: USB-C; USB-C_SMD-TYPE-C-31-M-12_1
J3: J3; RJ45-SMD_HR961160C
J4: DISP SH9; JST_SH_SM09B-SRSS-TB_1x09-1MP_P1.00mm_Horizontal
L1: L1; IND-SMD_L4.0-W4.0
PS1: B0505S-1W; PWRM-TH_B0505S-1W
Q1, Q2: MMBT3904; SOT-23
R1, R2, R6, R7, R11: 10k; R_0402_1005Metric
R3: 12k; R_0402_1005Metric
R4, R5: 330R; R_0402_1005Metric
R8, R9: 5k1; R_0402_1005Metric
R10: 45.3k; R_0402_1005Metric
R12: 120R; R_0805_2012Metric
R13, R15: 1k; R_0402_1005Metric
R14, R16, R17: 180R; R_0402_1005Metric
R18: 49.9R; R_0402_1005Metric
SW1: BOOT; SW_SPST_B3U-1000P
SW2: RST; SW_SPST_B3U-1000P
U1: ESP32-S3-WROOM-1-N8; ESP32-S3-WROOM-1
U2: W5500; LQFP-48_L7.0-W7.0-P0.50-LS9.0-BL
U3: U3; SOP-16_L10.0-W3.9-P1.27-LS6.0-BL
U4: SY8089; SOT-23-5_L3.0-W1.7-P0.95-LS2.8-BR
U5: U5; SOIC-16_L10.3-W7.5-P1.27-LS10.3-BL
Y1: 25MHz; Crystal_SMD_2520-4Pin_2.5x2.0mm

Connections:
+3V3: C1.1, C2.1, C8.1, C9.1, C10.1, C11.1, C15.1, C17.1, C18.1, J4.1, L1.2, R1.1, R2.1, R4.1, R5.1, R10.1, R18.2, U1.2, U2.4, U2.8, U2.11, U2.15, U2.17, U2.21, U2.28, U3.4, U3.16, U5.1
+5V: C16.1, C21.1, J2.A4B9, J2.B4A9, PS1.2, U4.1, U4.4
BUCK_FB: R10.2, R11.1, U4.5
BUCK_LX: L1.1, U4.3
CC1: J2.A5, R8.1
CC2: J2.B5, R9.1
DISP_CS: J4.7, U1.34
DISP_DC: J4.8, U1.35
DISP_MOSI: J4.6, U1.33
DISP_RST: J4.9, U1.31
DISP_SCK: J4.5, U1.32
DISP_SCL: J4.4, U1.5
DISP_SDA: J4.3, U1.4
DMX_A: D1.1, J1.3, R12.1, U5.11, U5.14
DMX_B: D1.3, J1.2, R12.2, U5.12, U5.13
DMX_EN: U1.12, U5.4, U5.5
DMX_RX: U1.11, U5.3
DMX_TX: U1.10, U5.6
DTR: Q1.2, R7.1, U3.13
EN: C3.1, Q1.3, R1.2, SW2.1, U1.3
ETH_ACTLED: J3.11, U2.27
ETH_CS: U1.18, U2.32
ETH_INT: U1.22, U2.36
ETH_LINKLED: J3.2, U2.25
ETH_RCT: C22.1, J3.6
ETH_RST: U1.17, U2.37
ETH_RXN: J3.8, U2.5
ETH_RXP: J3.7, U2.6
ETH_TCT: C14.1, J3.5, R18.1
ETH_TXN: J3.4, U2.1
ETH_TXP: J3.3, U2.2
GND: C1.2, C2.2, C3.2, C4.2, C5.2, C6.2, C8.2, C9.2, C10.2, C11.2, C12.2, C13.2, C14.2, C15.2, C16.2, C17.2, C18.2, C21.2, C22.2, D2.1, D3.1, D4.1, D5.1, D6.1, J2.1, J2.2, J2.3, J2.4, J2.A1B12, J2.B1A12, J3.10, J3.13, J3.14, J4.2, J4.MP, PS1.1, R3.2, R8.2, R9.2, R11.2, SW1.2, SW2.2, U1.1, U1.40, U1.41, U2.3, U2.9, U2.14, U2.16, U2.19, U2.29, U2.48, U3.1, U4.2, U5.2, U5.7, U5.8, Y1.2, Y1.4
GNDISO: C19.2, C20.2, D1.2, J1.1, PS1.3, U5.9, U5.10, U5.15
IO0: Q2.3, R2.2, SW1.1, U1.27
LED_B: R16.1, U1.7
LED_G: R14.1, U1.38
LED_R: R13.1, U1.39
LED_W: R17.1, U1.8
LED_Y: R15.1, U1.6
MISO: U1.21, U2.34
MOSI: U1.19, U2.35
unnamed: R3.1, U2.10
unnamed: J3.1, U2.18
unnamed: J3.12, R4.2
unnamed: Q1.1, R6.2
unnamed: D2.2, Q2.1, R7.2
unnamed: D3.2, R13.2
unnamed: D4.2, R14.2
unnamed: D5.2, R15.2
unnamed: D6.2, R16.2
RTS: Q2.2, R6.1, U3.14
S3_RX: U1.36, U3.2
S3_TX: U1.37, U3.3
SCLK: U1.20, U2.33
TOCAP: C6.1, U2.20
USB_DM: J2.A7, J2.B7, U3.6
USB_DP: J2.A6, J2.B6, U3.5
VISO: C19.1, C20.1, PS1.4, U5.16
W5500_1V2: C4.1, C5.1, U2.22
XI: C12.1, U2.30, Y1.1
XO: C13.1, U2.31, Y1.3

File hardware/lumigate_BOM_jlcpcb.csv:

Comment,Designator,Footprint,LCSC Part #
10uF 0805,C2,C_0805_2012Metric,C15850
1uF 0402 (EN power-on RC),C3,C_0402_1005Metric,C52923
1uF 0402,C4,C_0402_1005Metric,C52923
4.7uF 0402,C6,C_0402_1005Metric,C23733
22pF 0402,"C12,C13",C_0402_1005Metric,C1555
22uF 0805,"C16,C17",C_0805_2012Metric,C45783
10uF 1206,"C20,C21",C_1206_3216Metric,C13585
100nF 0402,"C1,C5,C8,C9,C10,C11,C14,C15,C18,C19,C22",C_0402_1005Metric,C1525
SM712 TVS SOT-23,D1,SOT-23,C404012
LED red 0603,D2,LED_0603_1608Metric,C2286
LED green 0603 KT-0603G,D3,LED_0603_1608Metric,C12624
LED yellow 0603 KT-0603Y,D4,LED_0603_1608Metric,C2287
LED blue 0603 KT-0603B,D5,LED_0603_1608Metric,C2288
LED white 0603,D6,LED_0603_1608Metric,C2290
XLR-3 out (XLR-328P),J1,CONN-TH_XLR-328P,C309326
USB-C data (TYPE-C-31-M-12),J2,USB-C_SMD-TYPE-C-31-M-12_1,C165948
RJ45 MagJack HR961160C SMD 10/100,J3,RJ45-SMD_HR961160C,C55683
JST SH 1.0mm 9-pin SMD (optional display; pre-crimped cables),J4,JST_SH_SM09B-SRSS-TB_1x09-1MP_P1.00mm_Horizontal,
2.2uH power inductor (CKCS4030),L1,IND-SMD_L4.0-W4.0,C354584
B0505S-1W iso DC-DC (EVISUN),PS1,PWRM-TH_B0505S-1W,C7465127
MMBT3904 SOT-23,"Q1,Q2",SOT-23,C20526
12k 0402 W5500 EXRES1 (12.4k spec OOS at LCSC; 12k within 100BASE-TX +-5%),R3,R_0402_1005Metric,C25752
330R 0402,"R4,R5",R_0402_1005Metric,C25104
5k1 0402,"R8,R9",R_0402_1005Metric,C25905
45.3k 0402 1% (buck FB top -> 3.32V),R10,R_0402_1005Metric,C137977
10k 0402,"R1,R2,R6,R7,R11",R_0402_1005Metric,C25744
120R 0805,R12,R_0805_2012Metric,C17437
150R 0402,"R14,R16,R17",R_0402_1005Metric,C25082
1k 0402,"R13,R15",R_0402_1005Metric,C11702
49.9R 1% 0402 W5500 TX center-tap bias (YAGEO RC0402FR-0749R9L),R18,R_0402_1005Metric,C87044
tact sw B3U-1000P,"SW1,SW2",SW_SPST_B3U-1000P,C231329
ESP32-S3-WROOM-1-N8 (8MB),U1,ESP32-S3-WROOM-1,C2913198
W5500 SPI Ethernet,U2,LQFP-48_L7.0-W7.0-P0.50-LS9.0-BL,C32843
CH340C USB-UART,U3,SOP-16_L10.0-W3.9-P1.27-LS6.0-BL,C84681
SY8089 buck 5->3.3V,U4,SOT-23-5_L3.0-W1.7-P0.95-LS2.8-BR,C78988
ISO3086DWR isolated RS-485,U5,SOIC-16_L10.3-W7.5-P1.27-LS10.3-BL,C183095
25MHz crystal 2520,Y1,Crystal_SMD_2520-4Pin_2.5x2.0mm,C2981622
